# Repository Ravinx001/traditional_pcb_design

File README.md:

<div align="center">
  <h1>🔢 Battery-Powered 2-Bit Binary Adder</h1>
  
  ### ⚡ Traditional PCB Design & Fabrication Project
  
  **Complete Electronics Design Lifecycle**  
  *Schematic Design • Chemical Etching • 3D-Printed Enclosure*

<br>

</div>

---

## 🎯 Project Overview

A complete electronics design project demonstrating a **2-bit binary adder** built from the ground up. This project encompasses schematic design, PCB layout, traditional chemical etching fabrication, and a custom 3D-printed enclosure.

The device accepts two 2-bit binary numbers via toggle switches, calculates the sum using a 4-bit binary adder IC, and displays the decimal result on a 7-segment LED display.

**Goal:** To design and fabricate a functional printed circuit board (PCB) using traditional home-lab procedures and integrate it into a finished consumer-like product.

<div align="center">

  <br>

</div>

---

## ✨ Key Features & Capabilities

### 🔌 **TTL/CMOS Logic Design**
Built using industry-standard 74-series TTL and CMOS logic integrated circuits for reliable digital operation.

### 🧮 **2-Bit Binary Addition**
- Input Range: 0-3 (per input)
- Output Range: 0-6 (sum display)
- Real-time calculation with instant display update

### 🔋 **Portable Battery Power**
9V battery operation with regulated 5V logic level via LM7805 voltage regulator.

### 📟 **7-Segment LED Display**
Clear decimal output using BCD-to-7-segment decoder for easy reading.

### 🏭 **Traditional Fabrication**
Handcrafted PCB using toner transfer and chemical etching methods.

---

## 🛠️ Hardware Architecture

<div align="center">

| **Component** | **Part Number** | **Function** |
|---------------|-----------------|--------------|
| **Binary Adder** | 74LS83 | 4-bit Binary Full Adder (configured for 2-bit) |
| **BCD Decoder** | CD4511 | BCD-to-7-Segment Latch/Decoder/Driver |
| **Display** | LTS-6960HR | 7-Segment LED Display |
| **Voltage Regulator** | LM7805 | 9V to 5V Regulation |
| **Input Switches** | Toggle Switches x4 | A0, A1 and B0, B1 Binary Inputs |
| **Filter Capacitors** | 100µF, 0.1µF, 0.22µF | Power Noise Suppression |

</div>

### 📊 Circuit Block Diagram

```
┌─────────────────────────────────────────────────────────────────┐
│                         POWER SUPPLY                            │
│  ┌──────────┐    ┌──────────┐    ┌────────────────────────────┐ │
│  │ 9V       │───▶│ LM7805   │───▶│ Filter Caps (100µF/0.1µF)  │ │
│  │ Battery  │    │ Regulator│    │         5V Output          │ │
│  └──────────┘    └──────────┘    └────────────────────────────┘ │
└─────────────────────────────────────────────────────────────────┘
                              │
                              ▼ 5V
┌─────────────────────────────────────────────────────────────────┐
│                        INPUT STAGE                              │
│  ┌────────────────────┐    ┌────────────────────┐               │
│  │ Switches A0, A1    │    │ Switches B0, B1    │               │
│  │ (Number A: 0-3)    │    │ (Number B: 0-3)    │               │
│  └─────────┬──────────┘    └─────────┬──────────┘               │
└────────────┼─────────────────────────┼──────────────────────────┘
             │                         │
             ▼                         ▼
┌─────────────────────────────────────────────────────────────────┐
│                      PROCESSING STAGE                           │
│                    ┌────────────────────┐                       │
│    A0, A1 ────────▶│     74LS83         │                       │
│    B0, B1 ────────▶│  4-bit Full Adder  │───▶ S0, S1, S2 (Sum)  │
│                    └────────────────────┘                       │
└─────────────────────────────────────────────────────────────────┘
                              │
                              ▼
┌─────────────────────────────────────────────────────────────────┐
│                       OUTPUT STAGE                              │
│  ┌────────────────────┐    ┌────────────────────┐               │
│  │      CD4511        │───▶│    LTS-6960HR      │               │
│  │  BCD-to-7-Segment  │    │  7-Segment Display │               │
│  │  Decoder/Driver    │    │    (Shows 0-6)     │               │
│  └────────────────────┘    └────────────────────┘               │
└─────────────────────────────────────────────────────────────────┘
```

---

## 🔧 Technical Designs

### 📐 Schematic
<div align="center">
  
</div>

*Full schematic designed in KiCad showing all component connections and signal flow.*

### 🖥️ PCB Layout
<div align="center">

</div>

*3D rendered views of the PCB showing component placement and copper traces.*

### 📦 3D Enclosure
<div align="center">
  
</div>

*Custom enclosure designed in Autodesk Fusion 360 with snap-fit design and dedicated cutouts.*

**[📥 Click here to view the 3D Model interactively (STL)](PCB_Enclosure_STL.stl)**

---

## ⚙️ Fabrication Process

This PCB was **not ordered from a fab house** but was handcrafted using traditional techniques:

<div align="center">

| **Step** | **Process** | **Details** |
|----------|-------------|-------------|
| 1️⃣ | **Design** | Layout created in KiCad with custom footprints |
| 2️⃣ | **Transfer** | Toner transfer method using heat to apply etch resist |
| 3️⃣ | **Etching** | Sulphuric/Ferric Acid solution to remove unwanted copper |
| 4️⃣ | **Drilling** | Manual drilling for through-hole components |
| 5️⃣ | **Assembly** | Component soldering and testing |
| 6️⃣ | **Enclosure** | 3D printed housing assembly |

</div>

### 🧪 Etching Chemistry
- **Etchant Options:** Ferric Chloride (FeCl₃) or Sulphuric Acid solution
- **Process Time:** 15-30 minutes depending on concentration and temperature
- **Safety:** Always use proper PPE (gloves, goggles, ventilation)

---

## 📦 Enclosure Design

A custom enclosure was designed in **Autodesk Fusion 360** to house the PCB and 9V battery.

### Features:
- ✅ Snap-fit/screw-mount design for easy assembly
- ✅ Dedicated cutouts for 7-segment display visibility
- ✅ Switch access holes with proper alignment
- ✅ Battery compartment with secure fit
- ✅ Ventilation slots for heat dissipation

### Printing Specifications:
| **Parameter** | **Value** |
|---------------|-----------|
| Material | PLA or ABS |
| Layer Height | 0.2mm |
| Infill | 20% |
| Supports | Minimal (for cutouts) |

---

## 🚀 How to Use

<div align="center">

| **Step** | **Action** |
|----------|------------|
| 1️⃣ | Toggle the **Power Switch** to ON |
| 2️⃣ | Use the **left pair of switches** to set the first number (0-3 binary) |
| 3️⃣ | Use the **right pair of switches** to set the second number (0-3 binary) |
| 4️⃣ | The **7-segment display** instantly shows the mathematical sum (0-6) |

</div>

### 🔢 Binary Input Reference

| **Switch Position** | **A1** | **A0** | **Decimal Value** |
|---------------------|--------|--------|-------------------|
| Both OFF | 0 | 0 | 0 |
| Right ON | 0 | 1 | 1 |
| Left ON | 1 | 0 | 2 |
| Both ON | 1 | 1 | 3 |

### 📊 Example Calculations

| **Input A** | **Input B** | **Sum** | **Display** |
|-------------|-------------|---------|-------------|
| 00 (0) | 00 (0) | 0 | 0 |
| 01 (1) | 01 (1) | 2 | 2 |
| 10 (2) | 11 (3) | 5 | 5 |
| 11 (3) | 11 (3) | 6 | 6 |

---

## 📁 File Structure

```
traditional_pcb_design/
├── 📄 README.md                     # Project documentation
├── 📄 LICENSE                       # Apache License 2.0
│
├── 🔧 KiCad Project Files
│   ├── Kicad_Project_Files.kicad_pro    # KiCad project file
│   ├── Kicad_Project_Files.kicad_sch    # Schematic design
│   ├── Kicad_Project_Files.kicad_pcb    # PCB layout
│   ├── Kicad_Project_Files.kicad_prl    # Project local settings
│   └── Kicad_Project_Files.svg          # Schematic SVG export
│
├── 📊 Documentation & Renders
│   ├── schematic.pdf                # Printable schematic
│   ├── pcb_board_print.pdf          # PCB print template for etching
│   ├── pcb_3d_top_view.png          # 3D render - top view
│   ├── pcb_3d_bottom_view.png       # 3D render - bottom view
│   └── PCB_Enclosure_3D_View.png    # Enclosure render
│
├── 📦 3D Enclosure Files
│   ├── PCB_Enclosure.f3z            # Fusion 360 source file
│   └── PCB_Enclosure_STL.stl        # 3D printable STL
│
├── 📸 Photos/                       # Build documentation photos
│   ├── PXL_20250615_190406250.jpg
│   ├── PXL_20250615_190418820.jpg
│   ├── PXL_20250615_190632909.jpg
│   ├── PXL_20250615_190721925.jpg
│   └── PXL_20250615_190739696.jpg
│
├── 📚 Libraries/                    # Custom KiCad libraries
│
└── 💾 Backups/
    ├── Kicad_Project_Files-backups/ # KiCad auto-backups
    └── SMP_2-bit_adder-backups/     # Additional backups
```

---

## 🛒 Bill of Materials (BOM)

<div align="center">

| **Qty** | **Component** | **Value/Part** | **Package** |
|---------|---------------|----------------|-------------|
| 1 | Binary Adder IC | 74LS83 | DIP-16 |
| 1 | BCD Decoder IC | CD4511 | DIP-16 |
| 1 | 7-Segment Display | LTS-6960HR | Common Cathode |
| 1 | Voltage Regulator | LM7805 | TO-220 |
| 4 | Toggle Switches | SPST | Through-hole |
| 1 | Power Switch | SPST | Through-hole |
| 1 | Electrolytic Capacitor | 100µF/16V | Radial |
| 2 | Ceramic Capacitor | 0.1µF | Through-hole |
| 1 | Ceramic Capacitor | 0.22µF | Through-hole |
| 7 | Current Limiting Resistors | 220Ω | 1/4W |
| 1 | 9V Battery Connector | Snap Connector | - |
| 1 | Copper Clad Board | Single-sided | 100x70mm |

</div>

---

## 📊 Technical Specifications

<div align="center">
  
| **Specification** | **Value** | **Notes** |
|-------------------|-----------|-----------|
| **Input Voltage** | 9V DC | Standard 9V battery |
| **Logic Voltage** | 5V DC | Regulated via LM7805 |
| **Power Consumption** | ~50mA | Display active |
| **Input Range** | 0-3 | Per 2-bit input |
| **Output Range** | 0-6 | Sum display |
| **PCB Size** | ~70x50mm | Single-layer |
| **Enclosure Size** | ~90x70x40mm | 3D printed |

</div>

---

## 🐛 Troubleshooting

<div align="center">

| **Problem** | **Possible Cause** | **Solution** |
|-------------|--------------------|--------------|
| No display | Power issue | Check battery, verify 5V at regulator output |
| Wrong number displayed | Wiring error | Verify BCD connections to display |
| Segments missing | Open circuit | Check segment resistors and solder joints |
| Inconsistent results | Floating inputs | Add pull-down resistors to unused inputs |
| Display too dim | Resistor value | Reduce current limiting resistor value |

</div>

---

## 🔧 Design Tools Used

<div align="center">

| **Tool** | **Version** | **Purpose** |
|----------|-------------|-------------|
| KiCad | 7.x+ | Schematic & PCB Design |
| Autodesk Fusion 360 | Latest | 3D Enclosure Design |
| GIMP/Inkscape | - | Image editing & SVG export |

</div>

---

## 🤝 Contributing

We welcome contributions! Whether it's bug fixes, feature enhancements, or documentation improvements:

1. Fork the Project
2. Create your Feature Branch (`git checkout -b feature/AmazingFeature`)
3. Commit your Changes (`git commit -m 'Add some AmazingFeature'`)
4. Push to the Branch (`git push origin feature/AmazingFeature`)
5. Open a Pull Request

### **Areas for Contribution**
- Extended bit-width designs (4-bit, 8-bit adders)
- Alternative display options (LCD, OLED)
- Different fabrication methods documentation
- Educational content and tutorials
- Enclosure design improvements

---

## 📚 Learning Outcomes

This project demonstrates proficiency in:

- ✅ **Digital Logic Design** - Understanding of binary arithmetic and IC operation
- ✅ **EDA Tools** - KiCad schematic capture and PCB layout
- ✅ **Traditional Fabrication** - Toner transfer and chemical etching
- ✅ **3D CAD Design** - Fusion 360 enclosure modeling
- ✅ **Electronics Assembly** - Through-hole soldering techniques
- ✅ **Documentation** - Technical writing and project presentation

---

## 📄 License

This project is licensed under the **Apache License 2.0** - see the [LICENSE](./LICENSE) file for details.

---

## 📞 Contact & Support

**Project Maintainer**  
📧 Email: [rav.business.lak@gmail.com]  
🐙 GitHub: [@Ravinx001](https://github.com/Ravinx001) <br>
💼 LinkedIn: [https://www.linkedin.com/in/ravindu-amarasekara/]

**Community**  
💬 Discussions: Use GitHub Discussions for questions  
🐛 Issues: Report bugs via GitHub Issues  

---

<div align="center">
  
  ### 🔢 **From Binary to Reality** 🔢
  ### 🌟 **Traditional Craftsmanship Meets Modern Design** 🌟
  
  ⭐ **Star this repository if you found it helpful!** ⭐
  
  **Built with ❤️ for the Electronics & Maker Community**

</div>

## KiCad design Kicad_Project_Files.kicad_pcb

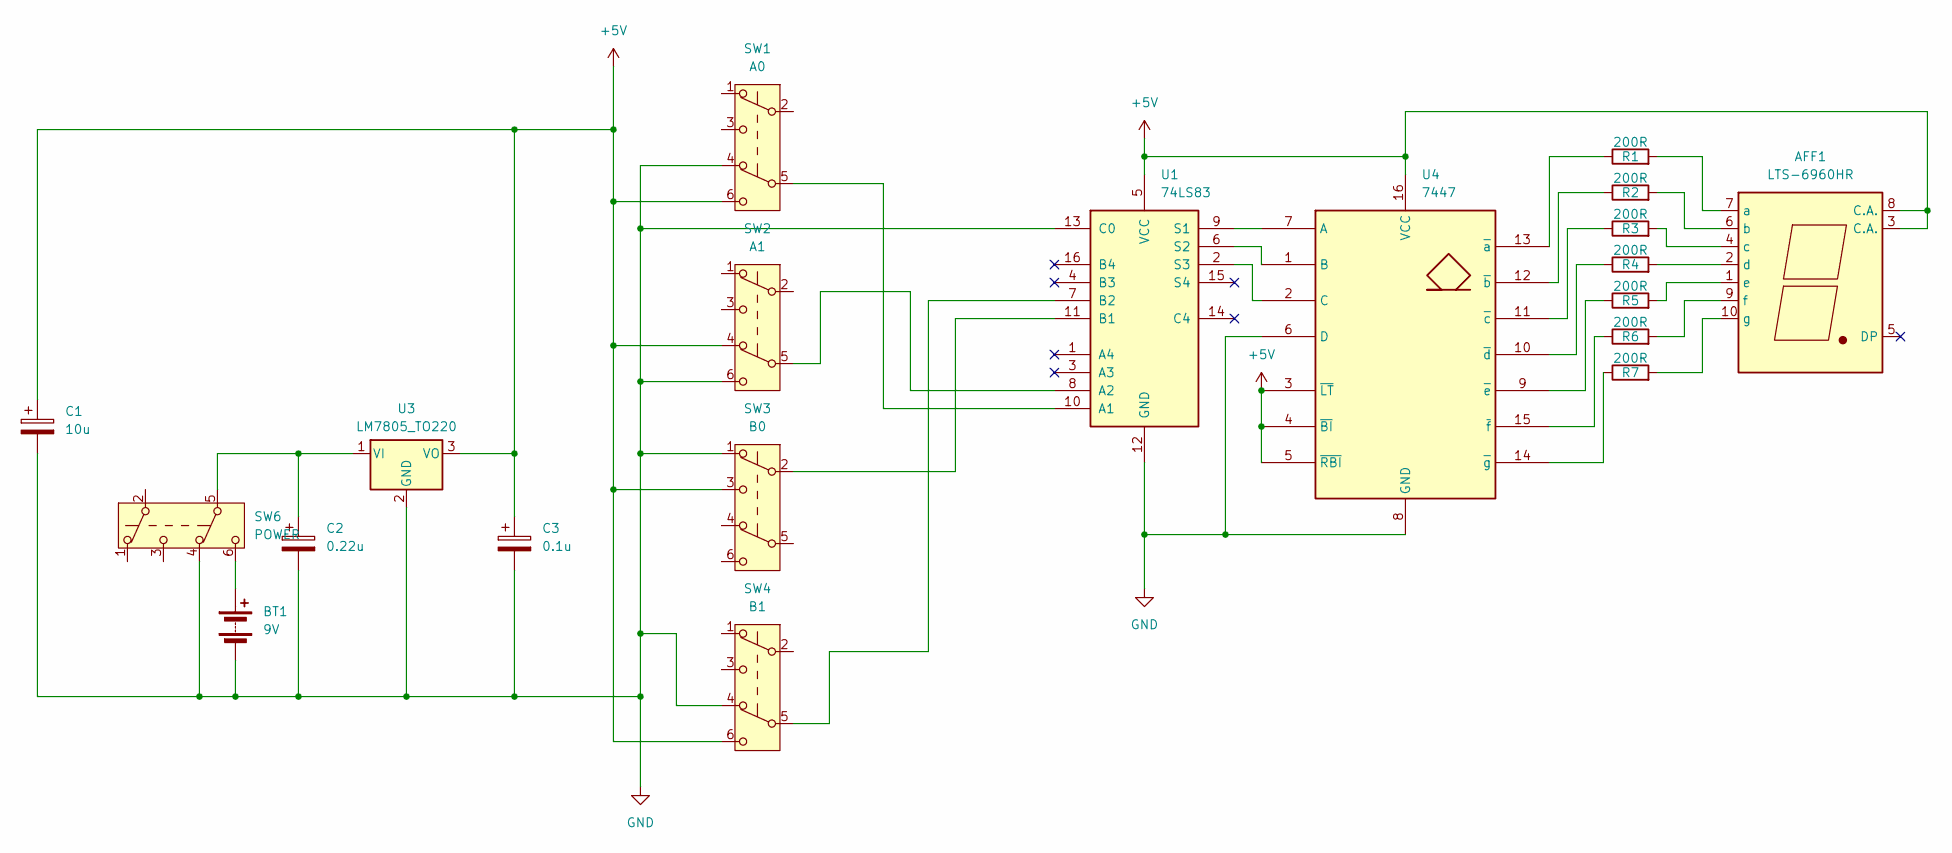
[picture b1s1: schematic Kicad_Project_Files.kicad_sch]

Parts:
AFF1: LTS-6960HR; 7SegmentLED_LTS6760_LTS6780
BT1: 9V; JST_XH_B2B-XH-A_1x02_P2.50mm_Vertical
C1: 10u; CP_Radial_D8.0mm_P3.50mm
C2: 0.22u; CP_Radial_D8.0mm_P3.50mm
C3: 0.1u; CP_Radial_D8.0mm_P3.50mm
R1, R2, R3, R4, R5, R6, R7: 200R; R_Axial_DIN0207_L6.3mm_D2.5mm_P7.62mm_Horizontal
SW1: A0; SW_Push_2P2T_Toggle_CK_PVA2xxH2xxxxxxV2
SW2: A1; SW_Push_2P2T_Toggle_CK_PVA2xxH2xxxxxxV2
SW3: B0; SW_Push_2P2T_Toggle_CK_PVA2xxH2xxxxxxV2
SW4: B1; SW_Push_2P2T_Toggle_CK_PVA2xxH2xxxxxxV2
SW6: POWER; SW_Push_2P2T_Toggle_CK_PVA2xxH2xxxxxxV2
U1: 74LS83; DIP-16_W7.62mm_Socket_LongPads
U3: LM7805_TO220; TO-220-3_Horizontal_TabDown
U4: 7447; DIP-16_W7.62mm_Socket_LongPads

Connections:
+5V: AFF1.3 (C.A.), AFF1.8 (C.A.), C1.1, C3.1, SW1.6 (C), SW2.4 (A), SW3.3 (C), SW4.6 (C), U1.5 (VCC), U3.3 (VO), U4.3 (~LT), U4.4 (~BI), U4.5 (~RBI), U4.16 (VCC)
GND: BT1.2 (-), C1.2, C2.2, C3.2, SW1.4 (A), SW2.6 (C), SW3.1 (A), SW4.4 (A), SW6.4 (A), U1.12 (GND), U1.13 (C0), U3.2 (GND), U4.6 (D), U4.8 (GND)
unnamed: AFF1.7 (a), R1.2
unnamed: AFF1.6 (b), R2.2
unnamed: AFF1.4 (c), R3.2
unnamed: AFF1.2 (d), R4.2
unnamed: AFF1.1 (e), R5.2
unnamed: AFF1.9 (f), R6.2
unnamed: AFF1.10 (g), R7.2
unnamed: BT1.1 (+), SW6.6 (C)
unnamed: SW1.5 (B), U1.10 (A1)
unnamed: SW2.5 (B), U1.8 (A2)
unnamed: SW3.2 (B), U1.11 (B1)
unnamed: SW4.5 (B), U1.7 (B2)
unnamed: U1.9 (S1), U4.7 (A)
unnamed: U1.6 (S2), U4.1 (B)
unnamed: U1.2 (S3), U4.2 (C)
unnamed: C2.1, SW6.5 (B), U3.1 (VI)
unnamed: R1.1, U4.13 (~a)
unnamed: R2.1, U4.12 (~b)
unnamed: R3.1, U4.11 (~c)
unnamed: R4.1, U4.10 (~d)
unnamed: R5.1, U4.9 (~e)
unnamed: R6.1, U4.15 (~f)
unnamed: R7.1, U4.14 (~g)

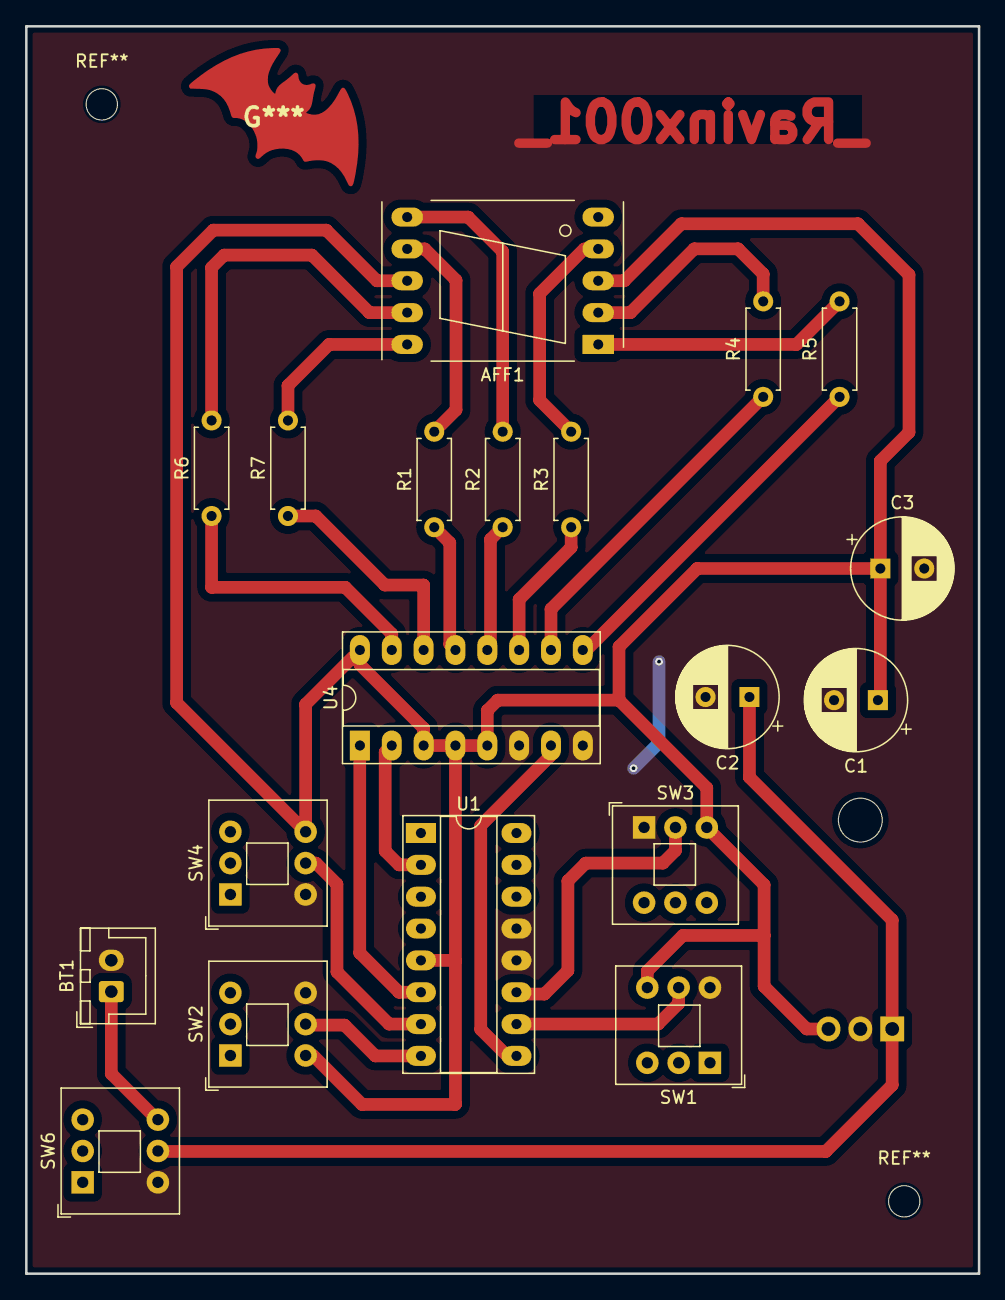
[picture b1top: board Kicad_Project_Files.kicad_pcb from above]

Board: 2 copper layers, 76.0 x 99.5 mm, 20 parts (1 on the bottom side), 25 nets.

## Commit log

2026-01-22 -- files uploaded
2026-01-22 --updated
